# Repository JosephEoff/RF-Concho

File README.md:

# RF-Concho
[A hat band for a nerd.](https://josepheoff.github.io/posts/1-hatband)

This project contains all the circuit diagrams and drawings needed to make a hat band with a passive cell phone detector.

The "range" is a  few centimeters at most - it isn't intended for any kind of serious measurement.

I made it because I could, and because the hat band on my fedora snapped.

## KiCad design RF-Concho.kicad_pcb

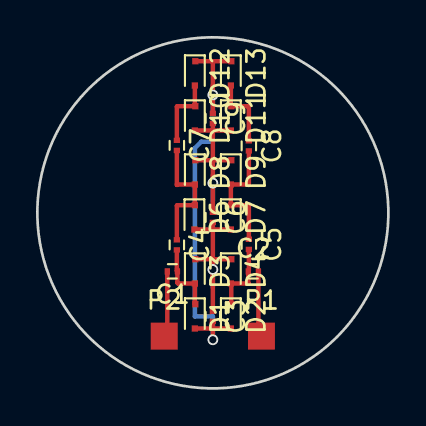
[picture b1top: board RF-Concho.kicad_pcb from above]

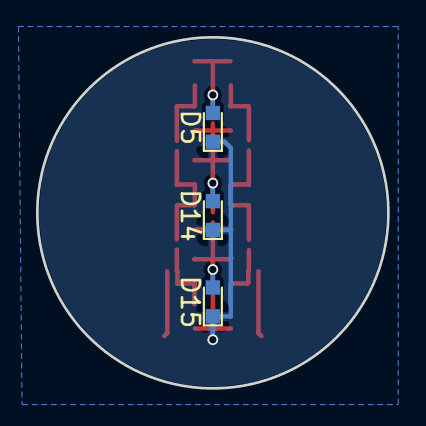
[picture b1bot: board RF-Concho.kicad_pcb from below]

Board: 2 copper layers, 19.5 x 19.5 mm, 26 parts (3 on the bottom side), 12 nets.

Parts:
C1, C2, C3, C4, C5, C6, C7, C8, C9: 10pF; C_0201
D1, D2, D3, D4, D6, D7, D8, D9, D10, D11, D12, D13: BAT63; D_SC-79
D5, D14, D15: APG1608SURKC; LED_0603
P1, P2: Ant; Measurement_Point_Square-SMD-Pad_Small

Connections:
unnamed: C1.1, C4.2, D1.1, D3.2
unnamed: C1.2, P2.1
unnamed: C2.1, C5.2, D2.1, D4.2
unnamed: C2.2, P1.1
unnamed: C3.1, C6.2, D3.1, D4.1, D6.2, D7.2, D15.2
unnamed: C3.2, D1.2, D2.2, D5.1, D14.1, D15.1
unnamed: C4.1, C7.2, D6.1, D8.2
unnamed: C5.1, C8.2, D7.1, D9.2
unnamed: C6.1, C9.2, D8.1, D9.1, D10.2, D11.2, D14.2
unnamed: C7.1, D10.1, D12.2
unnamed: C8.1, D11.1, D13.2
unnamed: C9.1, D5.2, D12.1, D13.1

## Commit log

2019-11-30 Created repository
2019-11-30 Removed unneeded photos.
2019-11-30 Create LICENSE
2019-11-30 Update to KiCad 5
2019-11-30 Added datasheets
2020-02-18 Added pictures
2020-02-18 Added link to project blog.
2020-02-18 Changed links.
